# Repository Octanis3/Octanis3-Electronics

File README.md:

# Octanis3-Electronics

Contains PCB files of the Owl Monitoring Device. More information on http://nestbox.octanis.org/

## Folders
* *_admin*: General administrative documents (e.g. Sponsoring documents, Project proposals etc.)
* *Nestbox_v1*: First PCB version with Lighbarrier, 13MHz RFID, (untested) LORA module
* *Nextbox_v2*: Second PCB version using 125-134 kHz RFID

## Dependencies
* Created with KiCAD 4.0.4 stable
* BOM created with bom2groupedCsv.xsl plugin by Wolf Walter.
* Schematic parts managed with https://github.com/BPJWES/KiCAD_Partslist_editor

2017

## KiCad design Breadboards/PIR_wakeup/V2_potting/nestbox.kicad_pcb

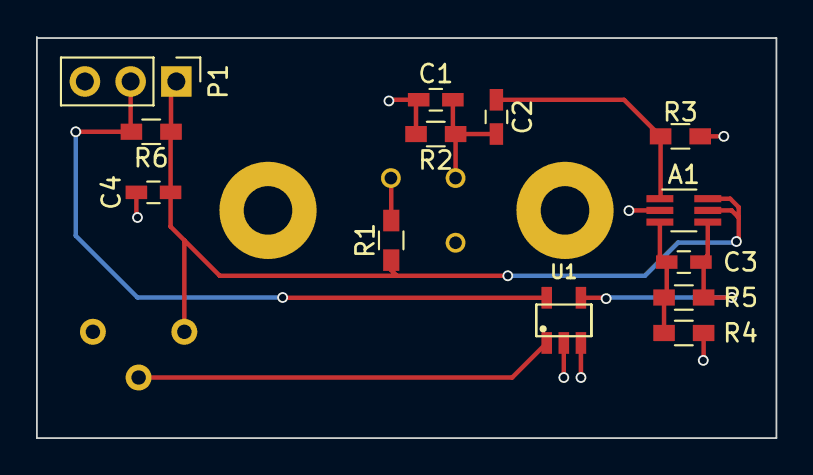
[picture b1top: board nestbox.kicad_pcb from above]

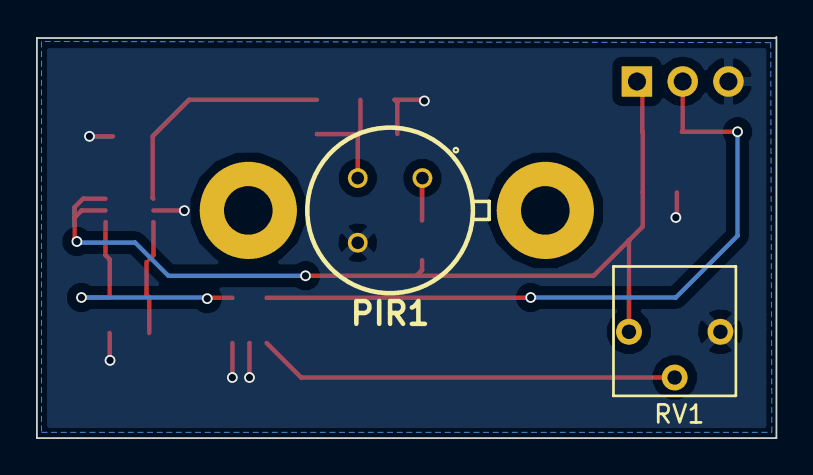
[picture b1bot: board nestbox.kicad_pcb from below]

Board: 2 copper layers, 41.1 x 22.3 mm, 15 parts (2 on the bottom side), 9 nets.

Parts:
A1: SOT-363_SC-70-6_Handsoldering
C1, C2, C3, C4: C_0603_HandSoldering
P1: Pin_Header_Straight_1x03_Pitch2.54mm
PIR1: IRA-S210ST01
R1, R2, R3, R4, R5, R6: R_0603_HandSoldering
RV1: Pot
U1: MAX9061

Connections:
GND: A1.2, C1.2, C4.2, P1.3, PIR1.3, R2.2, R3.2, R4.2, RV1.3, U1.2, U1.3
unnamed: A1.1, C2.1, R3.1
unnamed: A1.3, C3.2, R4.1, R5.2
unnamed: A1.4, C3.1, R5.1, U1.4
unnamed: A1.5, A1.6, C4.1, P1.1, R1.1, R6.1, RV1.1
unnamed: C1.1, C2.2, PIR1.2, R2.1
unnamed: P1.2, R6.2, U1.5
unnamed: PIR1.1, R1.2
unnamed: RV1.2, U1.1

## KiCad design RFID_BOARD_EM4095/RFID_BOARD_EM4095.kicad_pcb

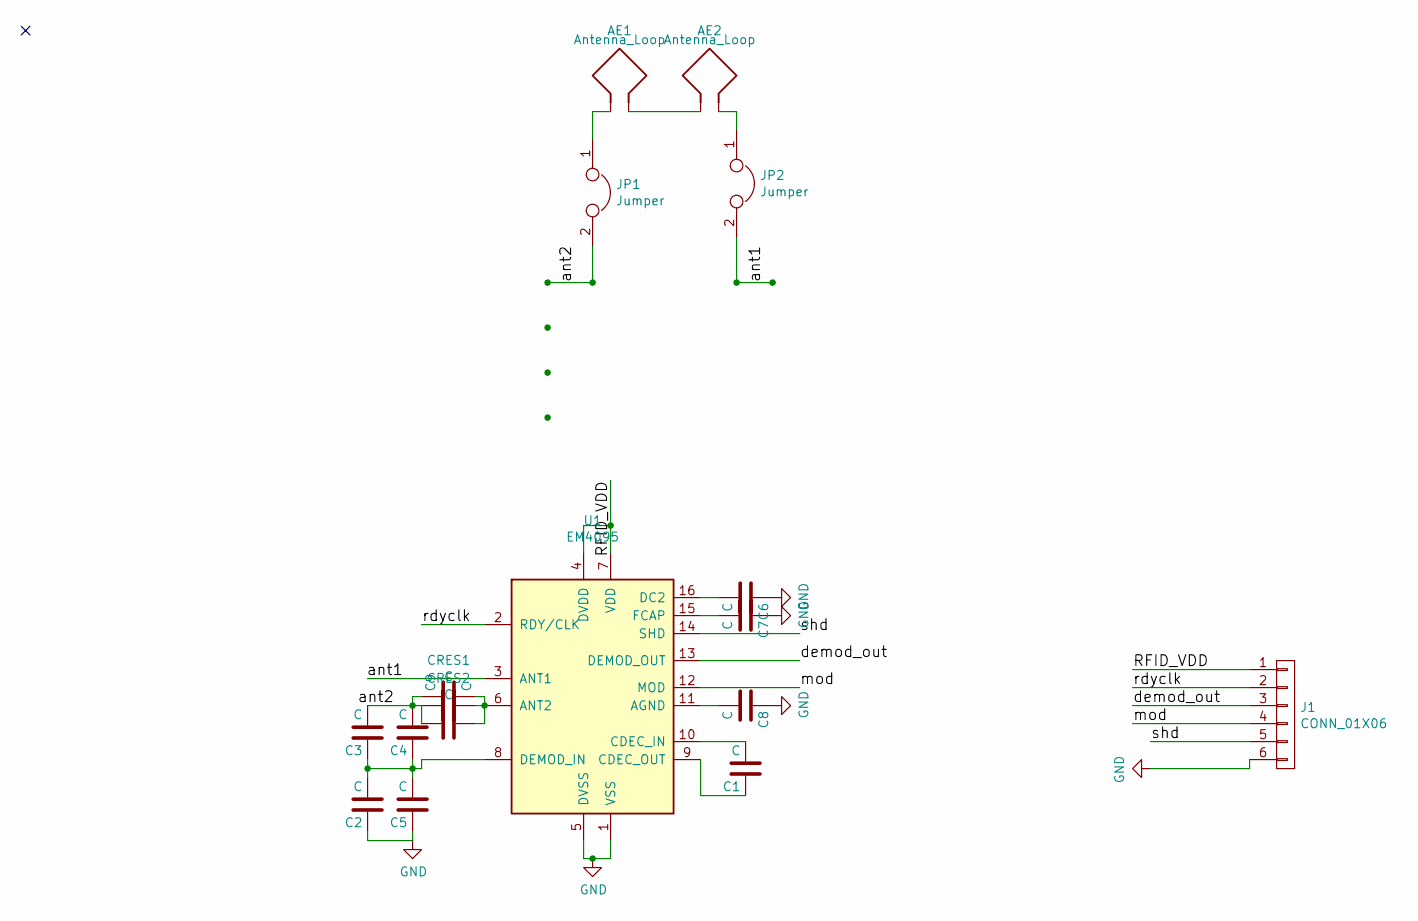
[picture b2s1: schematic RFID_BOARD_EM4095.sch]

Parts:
AE1, AE2: Antenna_Loop; 125kHz_PCB_Antenna
C1, C2, C3, C4, C5, C6, C7, C8, C9: C; C_0603
CRES1, CRES2: C; C_Rect_L7_W2_P5
J1: CONN_01X06; PINHEAD1-6
JP1, JP2: Jumper; Pin_Header_Straight_1x02_Pitch2.00mm
U1: EM4095; SOIC-16_3.9x9.9mm_Pitch1.27mm

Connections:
/RFID_VDD: J1.1, U1.4 (DVDD), U1.7 (VDD)
/ant1: JP2.2, U1.3 (ANT1)
/ant2: C3.2, C4.2, C9.1, CRES1.2, CRES2.2, JP1.2; also elsewhere on the board
/demod_out: J1.3, U1.13 (DEMOD_OUT)
/mod: J1.4, U1.12 (MOD)
/rdyclk: J1.2, U1.2 (RDY/CLK)
/shd: J1.5, U1.14 (SHD)
GND: C2.1, C5.1, C6.1, C7.1, C8.1, J1.6, U1.1 (VSS), U1.5 (DVSS)
unnamed: AE1.1, JP1.1
unnamed: AE1.2, AE2.2
unnamed: AE2.1, JP2.1
unnamed: C1.1, U1.9 (CDEC_OUT)
unnamed: C1.2, U1.10 (CDEC_IN)
unnamed: C2.2, C3.1, C4.1, C5.2, U1.8 (DEMOD_IN)
unnamed: C6.2, U1.16 (DC2)
unnamed: C7.2, U1.15 (FCAP)
unnamed: C8.2, U1.11 (AGND)
unnamed 17: C9.2, CRES1.1, CRES2.1, U1.6 (ANT2); also elsewhere on the board

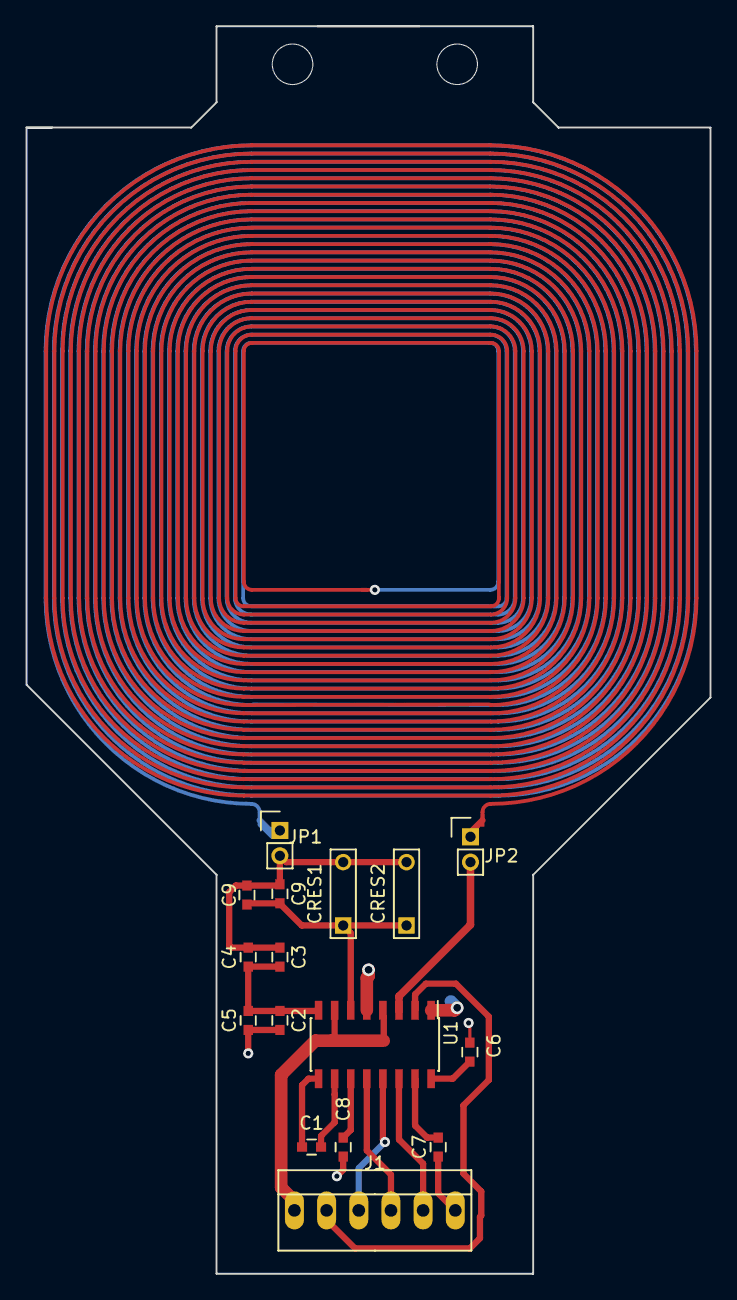
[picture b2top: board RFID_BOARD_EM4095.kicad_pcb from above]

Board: 2 copper layers, 54.0 x 98.5 mm, 18 parts (1 on the bottom side), 18 nets.

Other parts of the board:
C9#2: C; C_0603

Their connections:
/ant2: C9#2.1; also elsewhere on the board
unnamed 17: C9#2.2; also elsewhere on the board

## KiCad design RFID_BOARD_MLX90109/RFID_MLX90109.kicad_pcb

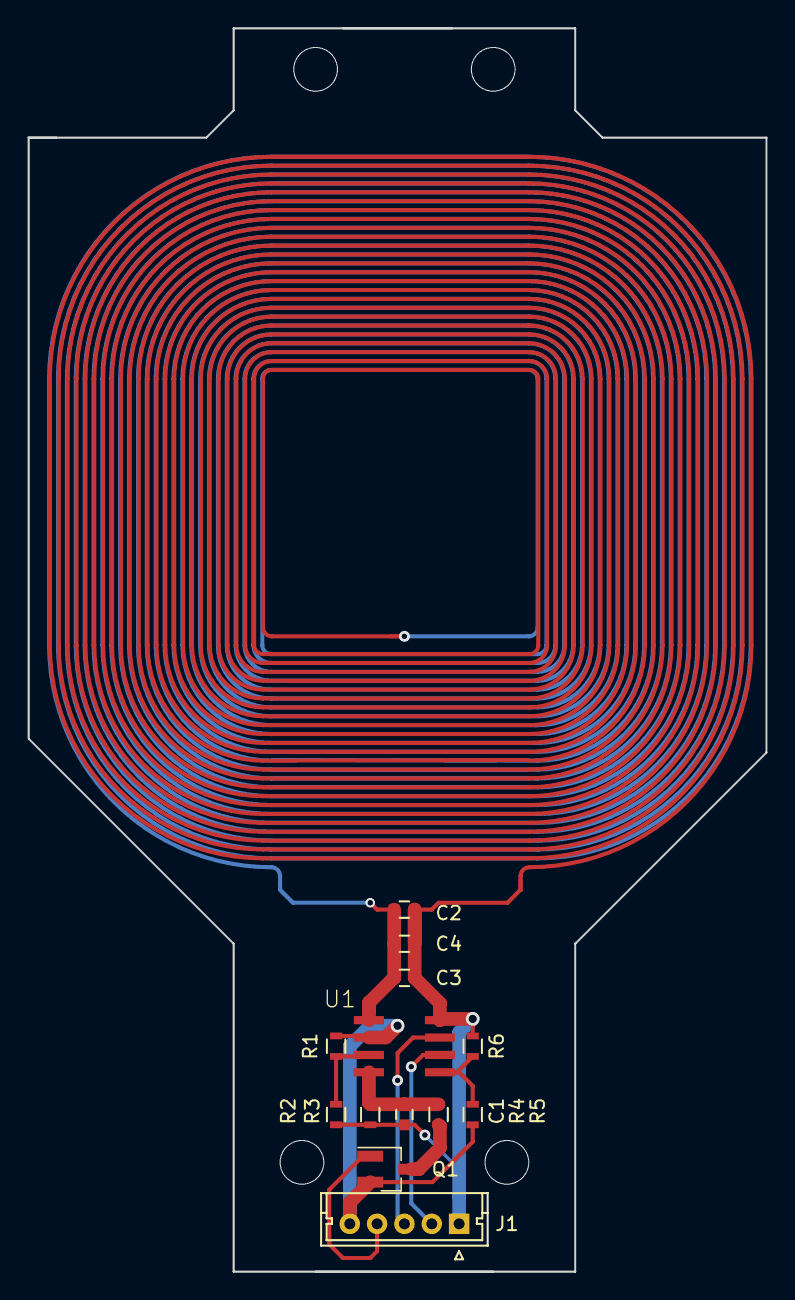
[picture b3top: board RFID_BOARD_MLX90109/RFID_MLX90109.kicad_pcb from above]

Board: 2 copper layers, 54.0 x 91.0 mm, 15 parts (1 on the bottom side), 11 nets.

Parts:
AE1, AE2: Antenna_Loop; 125kHz_PCB_Antenna
C1, C2, C3, C4: C; C_0603
J1: CONN_01X05; Molex_MicroLatch-53253-0570_05x2.00mm_Straight
Q1: Q_NMOS_GSD; SOT-23_Handsoldering
R1, R2, R5, R6: R; R_0603
R3: 100k; R_0603
R4: 36k; R_0603
U1: MLX90109; SO8

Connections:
/RFID_ANT: AE1.1, C2.2, C3.2, C4.2, U1.1
/RFID_CLOCK: J1.2, U1.6
/RFID_DATA: J1.3, U1.7
/RFID_MODE: R5.2, R6.1, U1.5
/RFID_SPEED: R1.1, R2.1, U1.3
/RFID_VDD: AE2.1, C1.2, C2.1, C3.1, C4.1, J1.1, R2.2, R3.2, R6.2, U1.8
GND: J1.5, Q1.2, R1.2, R5.1, U1.2
unnamed: AE1.2, AE2.2
unnamed: C1.1, R3.1, R4.2, U1.4
unnamed: Q1.3, R4.1
RFID_MODU_N: J1.4, Q1.1

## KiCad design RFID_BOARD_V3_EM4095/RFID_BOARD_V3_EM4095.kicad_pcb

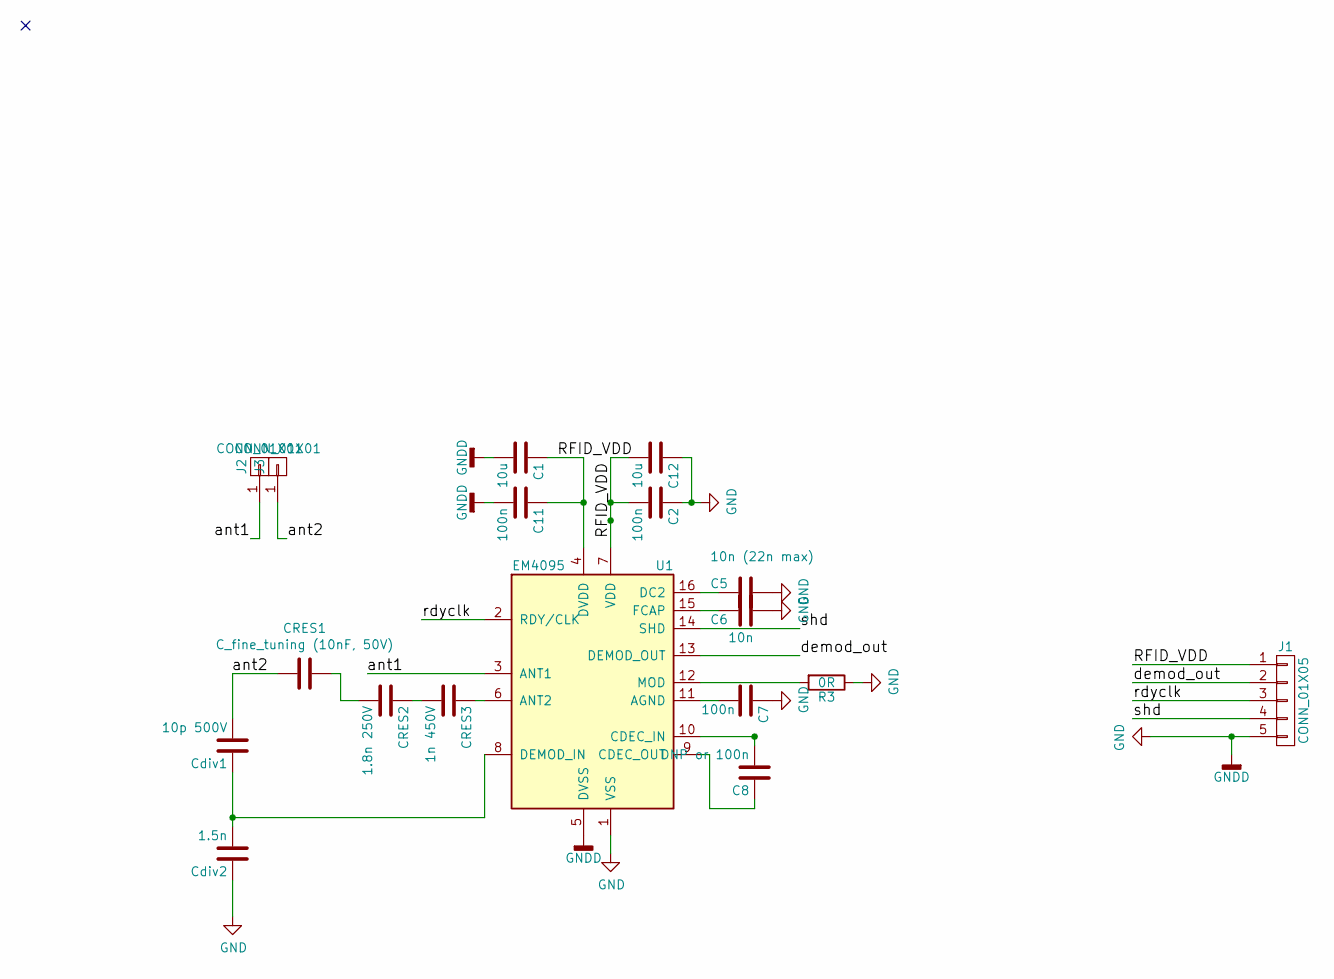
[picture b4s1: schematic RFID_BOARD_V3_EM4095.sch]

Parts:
C1, C12: 10u; C_0805
C2, C7, C11: 100n; C_0603
C5: 10n (22n max); C_0603
C6: 10n; C_0603
C8: DNP or 100n; C_0603
CRES1: C_fine_tuning (10nF, 50V); C_0603
CRES2: 1.8n 250V; C_0805; MPN C0805C182JAGAC
CRES3: 1n 450V; C_0805; MPN C0805C102JAGACTU or CC0805JKNPOBBN102
Cdiv1: 10p 500V; C_0805; MPN C0805C100KBRACTU
Cdiv2: 1.5n; C_0603
J1: CONN_01X05; Pin_Header_Straight_1x05_Pitch2.54mm
J2, J3: CONN_01X01; Measurement_Point_Square-SMD-Pad_Small
R3: 0R; R_0603
U1: EM4095; SOIC-16_3.9x9.9mm_Pitch1.27mm

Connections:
/RFID_VDD: C1.1, C2.2, C11.1, C12.2, J1.1, U1.4 (DVDD), U1.7 (VDD)
/ant1: J2.1, U1.3 (ANT1)
/ant2: CRES1.2, Cdiv1.2, J3.1
/demod_out: J1.2, U1.13 (DEMOD_OUT)
/rdyclk: J1.3, U1.2 (RDY/CLK)
/shd: J1.4, U1.14 (SHD)
GND: C1.2, C2.1, C5.1, C6.1, C7.1, C11.2, C12.1, Cdiv2.1, J1.5, R3.1, U1.1 (VSS), U1.5 (DVSS)
unnamed: C5.2, U1.16 (DC2)
unnamed: C6.2, U1.15 (FCAP)
unnamed: C7.2, U1.11 (AGND)
unnamed: C8.1, U1.9 (CDEC_OUT)
unnamed: C8.2, U1.10 (CDEC_IN)
unnamed: CRES1.1, CRES2.2
unnamed: CRES2.1, CRES3.2
unnamed: CRES3.1, U1.6 (ANT2)
unnamed: Cdiv1.1, Cdiv2.2, U1.8 (DEMOD_IN)
unnamed: R3.2, U1.12 (MOD)

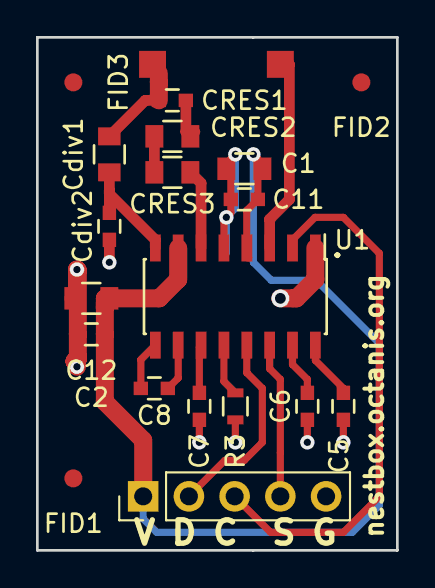
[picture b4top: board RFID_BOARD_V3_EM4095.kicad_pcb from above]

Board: 2 copper layers, 20.0 x 28.5 mm, 21 parts (0 on the bottom side), 17 nets.

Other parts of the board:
FID1, FID2, FID3: Fiducial_1mm_Dia_2.54mm_Outer_CopperTop

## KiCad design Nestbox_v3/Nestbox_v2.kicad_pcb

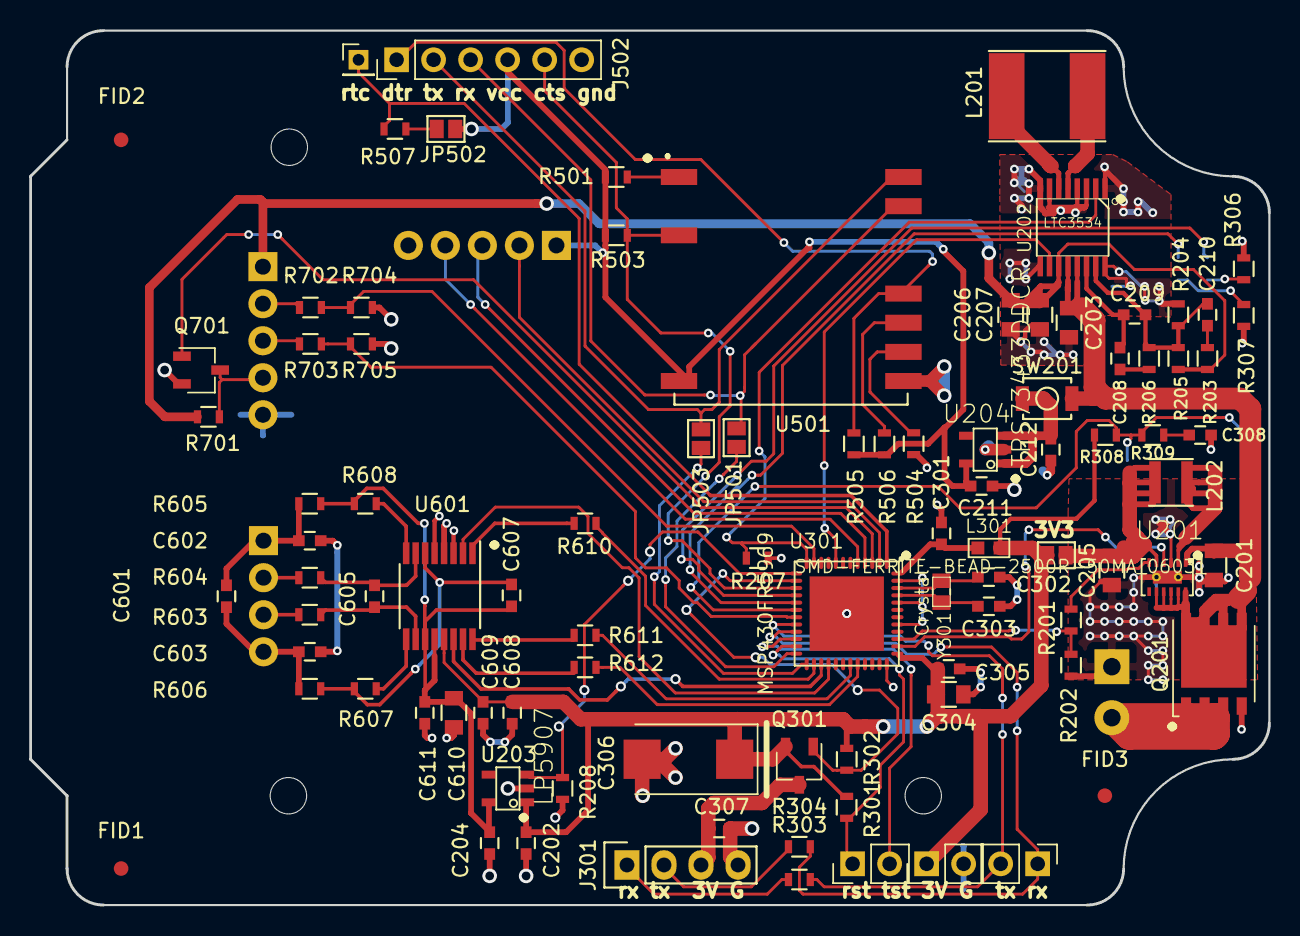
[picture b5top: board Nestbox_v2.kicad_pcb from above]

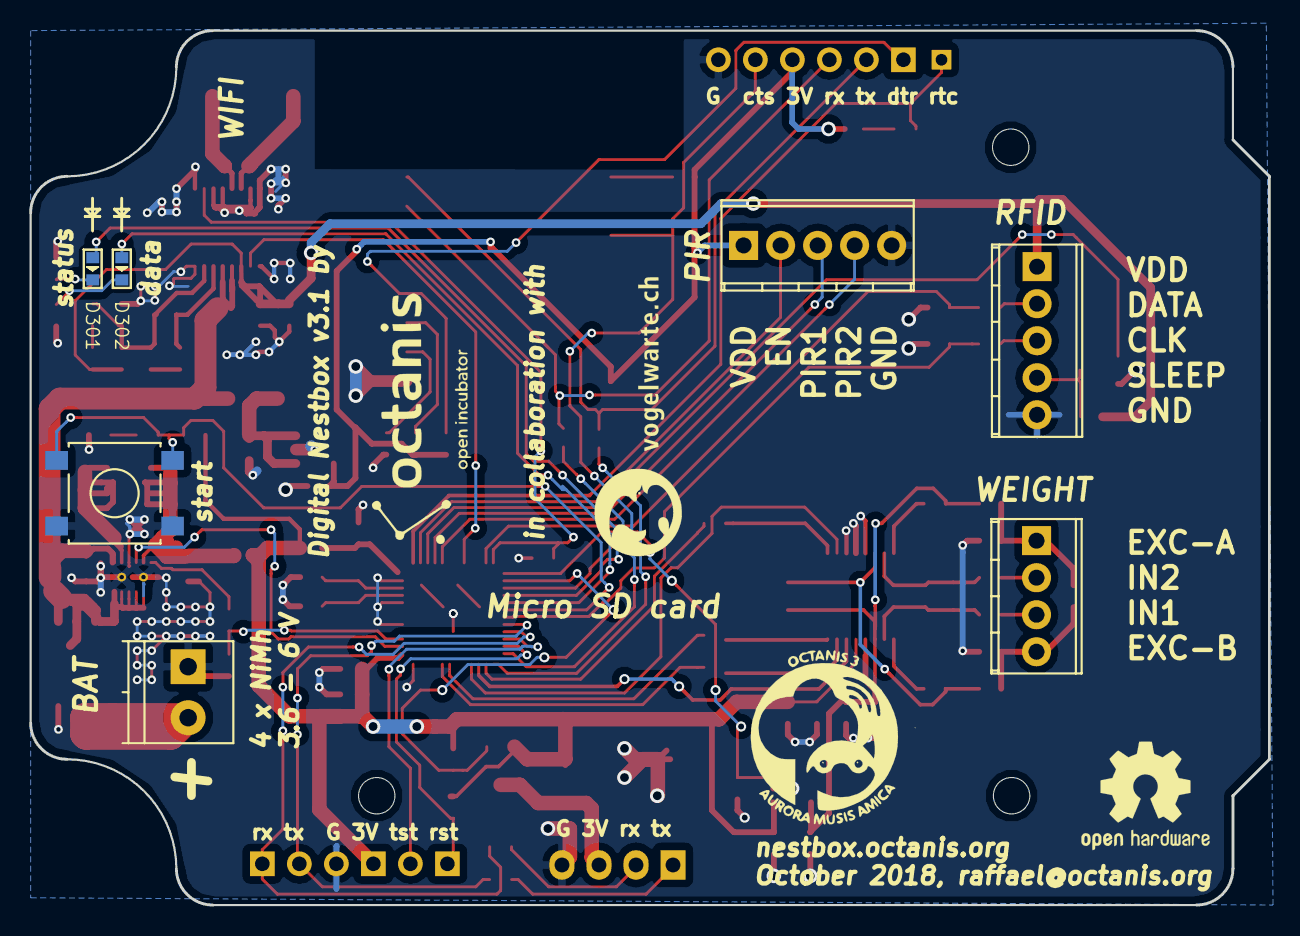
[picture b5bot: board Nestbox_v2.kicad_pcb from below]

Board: 2 copper layers, 85.0 x 60.0 mm, 100 parts (7 on the bottom side), 76 nets.

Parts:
C201, C203, C205, C206, C207, C304, C610: 10u; C_0805
C202, C204, C212, C601, C607, C608: 1u; C_0603
C208: 330p; C_0603
C209: 10p; C_0603
C210: 33p; C_0603
C211: 2.2u; C_0603
C301, C305, C307, C308, C609: 100n; C_0603
C302, C303: 25p; C_0603
C306: 100u; CP_Tantalum_Case-D_EIA-7343-31_Reflow
C602, C603: 100n 1%; C_0603
C605: 100n 1% DNP; C_0603
C611: 10n; C_0603
D301: SMD-LED-CLEAR-GREEN_0603_; LED-0603
D302: SMD-LED-CLEAR-BLUE_0603_; LED-0603
FID1, FID2, FID3: Fiducial_1mm_Dia_2.54mm_Outer_CopperTop
J201: BATT_CONN_01X02; TerminalBlock_Pheonix_PT-3.5mm_2pol
J301: CONN_01X04; Pin_Header_Straight_1x04
J402: CONN_01X05; TerminalBlock_Pheonix_MPT-2.54mm_5pol
J502: CONN_01X06; Pin_Header_Straight_1x06_Pitch2.54mm
J601: LOAD_CELL_CONN_01X04; TerminalBlock_Pheonix_MPT-2.54mm_4pol
J701: RFID_CONN_01X05; TerminalBlock_Pheonix_MPT-2.54mm_5pol
JP203: Jumper_3V3; GS2
JP501, JP502, JP503: Jumper; GS2
L201: 5uH; Inductor_Taiyo-Yuden_NR-60xx_HandSoldering
L202: 4.7uH; Inductor_Taiyo-Yuden_NR-30xx
L301: SMD-FERRITE-BEAD-2500R-50MA_0603_; L0603
P301: RX/TX; Socket_Strip_Straight_1x02_Pitch2.54mm
P302: TST/RST; Socket_Strip_Straight_1x02_Pitch2.54mm
P303: DEBUG_3V3; Socket_Strip_Straight_1x02_Pitch2.54mm
Q201: TPH1R712MDL1Q; TDSON-8-1_HandSoldering
Q301: NTR3A052PZT1G; TSOT-23
Q701: DMG3402L; TSOT-23
R201, R207, R208, R302, R507, R701, R704, R705: 82k; R_0603
R202, R301, R702, R703: 47k; R_0603
R203, R308, R309, R501, R503, R504, R505, R506: 10k; R_0603
R204: 162k 1%; R_0603
R205: 649k 1%; R_0603
R206: 15k; R_0603
R303, R304: 0R; R_0603
R306, R307: 1k; R_0603
R603, R604: 1k 1% --> short to 0R; R_0603
R605, R606: 100R 1%; R_0603
R607, R608: DNP; R_0603
R610, R611, R612: 47R; R_0603
SW201: external_button; SW_SPST_B3U-1000P
SW301: SMD-BUTTON_2P-3.0X2.5X1.2+0.4MM_; SW_SPST_B3S-1000
TP_RTC301: CONN_01X01; Socket_Strip_Straight_1x01_Pitch2.00mm
U201: TPS62745; WSON_3x2mm_12pin
U202: LTC3534; SSOP16-0.635-5X4MM
U203: LP5907; SOT23-5
U204: TPS73433DDCR; SOT23-5
U301: MSP430FR5969; S-PVQFN-N48
U501: ESP-12S; ESP-12E_SMD_UART_ONLY
U601: ADS1220; TSSOP-16_4.4x5mm_Pitch0.65mm
Y301: Crystal; X2-SMD-L2.0X1.2X0.55MM

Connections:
+3V3: C202.1, C304.2, C305.2, C306.1, C608.1, C609.2, JP203.2, L301.2, P303.1, Q301.2, R301.2, R302.1, R308.1, U203.1, U301.37, U601.13
+5V: C206.1, C207.1, J701.1, R203.2, R205.1, R701.2, U202.11
+BATT: C201.1, C203.1, Q201.3, SW201.1, U201.1, U201.8, U201.9, U201.10, U201.11, U201.12, U202.12, U202.13
/Communication/DTR: J502.1, R505.2, U501.12
/Communication/ESP12_ENABLE: J502.5, R503.1, U301.15, U501.3
/Communication/ESP12_RX: JP501.1, U301.24
/Communication/ESP12_TX: JP503.1, U301.25
/Communication/ESP12_VCC_sense: R507.2, TP_RTC301.1, U301.1
/Communication/RX: J502.3, JP501.2, U501.15
/Communication/TX: J502.2, JP503.2, U501.16
/Control/5V_ENABLE: R207.2, U202.2, U301.12
/Control/AVCC: C301.1, L301.1, U301.48
/Control/BAT_TEST_ENABLE: U201.4, U301.38
/Control/DBG_LED1: D301.+, U301.16
/Control/DBG_LED2: D302.+, U301.17
/Control/DBG_Switch: R308.2, R309.1, SW301.2, U301.18
/Control/HK_BAT_V: R201.1, R202.2, U301.39
/Control/LOADCELL_SPI_CS: U301.28, U601.2
/Control/RFID_CLK: R702.1, R704.2, U301.11
/Control/RFID_DATA: R703.2, R705.1, U301.19
/Control/RFID_SLEEP_N: Q701.1, U301.3
/Control/RX: P301.1, R304.1, U301.21
/Control/SD_CARD_ENABLE: Q301.1, R302.2, U301.14
/Control/SPI_CLK: R610.1, U301.26
/Control/SPI_MISO: R612.1, U301.32
/Control/SPI_MOSI: R611.1, U301.31
/Control/TX: P301.2, R303.1, U301.20
/Load_Cell/AIN1: C605.1, R603.1, U601.10
/Load_Cell/AIN2: C605.2, R604.1, U601.7
/Load_Cell/DRDY_N: U301.27, U601.14
/Load_Cell/EXC_A: C601.1, C602.1, J601.1, R605.2
/Load_Cell/EXC_B: C601.2, C603.1, J601.4, R606.2
/Load_Cell/conn2: J601.2, R604.2
/Load_Cell/conn3: J601.3, R603.2
/PIR_EN: J402.2, U301.2
/PIR_OUT1: J402.3, U301.4
/PIR_OUT2: J402.4, U301.5
/Power/5V_PWM: U202.10, U301.8
/Power/LDO_EN: R208.2, U203.3, U301.13
/Power/batt_in: J201.2, Q201.1
GND: C201.2, C202.2, C203.2, C204.2, C205.2, C206.2, C207.2, C211.2, C212.2, C301.2, C302.2, C303.2, C304.1, C305.1, C306.2, C307.2, C308.2, C602.2, C603.2, C608.2, C609.1, C610.1, C611.1, J201.1, J301.4, J402.5, J502.6, J701.5, P303.2, Q201.2, Q701.2, R202.1, R204.1, R207.1, R208.1, R306.2, R307.2, R504.1, R704.1, R705.2, SW301.1, U201.3, U201.GND1, U201.GND2, U202.1, U202.3, U202.4, U202.7, U202.8, U202.9, U202.16, U203.2, U204.2, U301.36, U301.41, U301.44, U301.47, U301.VSS_, U501.9, U601.3, U601.4, U601.5
unnamed: C205.1, JP203.1, L202.2, U201.5
unnamed: C208.1, R206.1
unnamed: C208.2, C209.2, U202.14
unnamed: C209.1, C210.2, R204.2, R205.2, R206.2, U202.15
unnamed: C210.1, R203.1
unnamed: C212.1, SW201.2, U204.1, U204.3
unnamed: C302.1, U301.46, Y301.1
unnamed: C303.1, U301.45, Y301.2
unnamed: C307.1, J301.3, Q301.3
unnamed: C308.1, R309.2
unnamed: C607.2, R606.1, R607.2, U601.6
unnamed: D301.-, R306.1
unnamed: D302.-, R307.1
unnamed: J301.1, R303.2
unnamed: J301.2, R304.2
unnamed: J701.2, R702.2
unnamed: J701.3, R703.1
unnamed: J701.4, Q701.3, R701.1
unnamed: JP502.2, R507.1
unnamed: L201.1, U202.5
unnamed: L201.2, U202.6
unnamed: L202.1, U201.2
unnamed: P302.1, R301.1, U301.23
unnamed: P302.2, U301.22
unnamed: R201.2, U201.6
unnamed: R501.2, U501.1
unnamed: R504.2, U501.10
unnamed: R506.2, U501.11
unnamed: R607.1, U601.9
unnamed: R608.1, U601.8
unnamed: R610.2, U601.1
unnamed: R611.2, U601.16
unnamed: R612.2, U601.15
VAA: C204.1, C607.1, C610.2, C611.2, R605.1, R608.2, U203.5, U601.11, U601.12
VDDA: C211.1, J402.1, J502.4, JP502.1, R501.1, R503.2, R505.1, R506.1, U204.5, U501.8

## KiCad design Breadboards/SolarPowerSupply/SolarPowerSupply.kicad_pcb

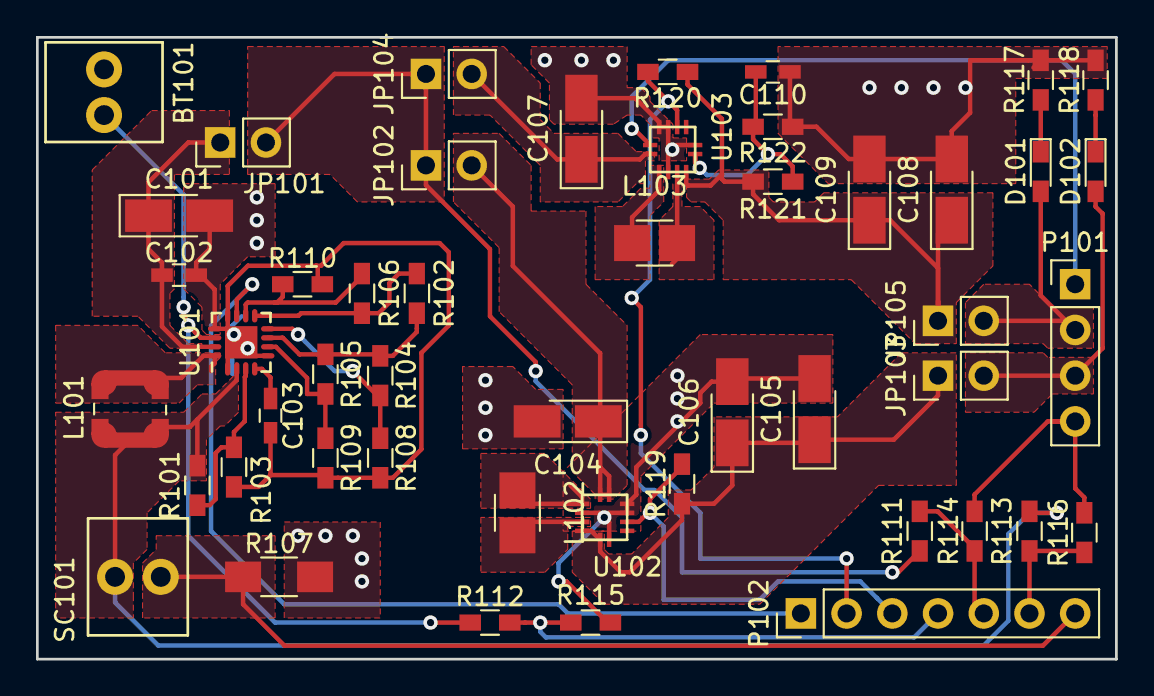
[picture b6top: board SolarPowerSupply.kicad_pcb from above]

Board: 2 copper layers, 59.9 x 34.5 mm, 49 parts (0 on the bottom side), 34 nets.

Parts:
BT101: Battery; TE_282834-2
C101: 4.7u; C_SMD_2012_Hand
C102: 100n; C_0603_HandSoldering
C103: 10n; C_0603_HandSoldering
C104, C105, C106, C107, C108, C109: 10u; C_SMD_2012_Hand
C110: 10p; C_0603_HandSoldering
D101, D102: LED; LED_0603_HandSoldering
JP101, JP102, JP103, JP104, JP105: Jumper; Pin_Header_Straight_1x02_Pitch2.54mm
L101: 22u; L_Wuerth_WE-TPC-3816
L102, L103: 1.5u; L_2520_HandSoldering
P101: CONN_01X04; Pin_Header_Straight_1x04_Pitch2.54mm
P102: CONN_01X07; Pin_Header_Straight_1x07_Pitch2.54mm
R101, R102, R103, R104, R105, R106, R108, R109, R110, R111, R112, R113, R114, R115, R116, R117, R118, R121, R122: R; R_0603_HandSoldering
R107: 1E; R_1206_HandSoldering
R119, R120: 1M; R_0603_HandSoldering
SC101: Solar_Cells; TE_282834-2
U101: bq25504; QFN-16-1EP_3x3mm_Pitch0.5mm
U102: TPS63051; VQFN_12_2.5x2.5mm
U103: TPS63050; VQFN_12_2.5x2.5mm

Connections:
5V_Enable: P101.1, U103.11
+3V3: D102.2, JP103.2, P101.3
+5V: D101.2, JP105.2, P101.2
/VBat: BT101.1, R112.1, U101.14
/VBus: JP101.2, JP102.1, JP104.1, R111.1
/VSolar: L101.1, R101.1, R113.1, SC101.1, U101.2
BAT_OK: P102.1, U101.11
GND: BT101.2, C101.2, C102.2, C103.2, C104.2, C105.2, C106.2, C107.2, C108.2, C109.2, C110.2, P101.4, R103.2, R107.2, R108.2, R109.2, R110.2, R114.2, R115.2, R116.2, R117.2, R118.2, R122.1, U101.1, U101.5, U101.12, U101.13, U101.17, U102.2, U102.6, U102.9, U102.10, U103.2, U103.6, U103.9, U103.10
HK_BAT_V: P102.4, R112.2, R115.1
HK_BUS_V: P102.5, R111.2, R114.1
HK_SOLAR_I: P102.7, R107.1, SC101.2
HK_SOLAR_V: P102.6, R113.2, R116.1
unnamed: C101.1, C102.1, JP101.1, U101.15
unnamed: C103.1, U101.4
unnamed: C104.1, JP102.2, U102.11, U102.12
unnamed: C105.1, C106.1, JP103.1, R119.1, U102.4, U102.5
unnamed: C107.1, JP104.2, U103.12
unnamed: C108.1, C109.1, JP105.1, R120.1, R121.1, U103.4
unnamed: C110.1, R121.2, R122.2, U103.5
unnamed: D101.1, R117.1
unnamed: D102.1, R118.1
unnamed: L101.2, U101.16
unnamed: L102.1, U102.1
unnamed: L102.2, U102.3
unnamed: L103.1, U103.1
unnamed: L103.2, U103.3
unnamed: R101.2, R103.1, U101.3
unnamed: R102.1, R104.1, R105.1, U101.7
unnamed: R102.2, R106.1, U101.9
unnamed: R104.2, R108.1, U101.8
unnamed: R105.2, R109.1, U101.6
unnamed: R106.2, R110.1, U101.10
PGOOD_3.3: P102.3, R119.2, U102.8
PGOOD_5: P102.2, R120.2, U103.8

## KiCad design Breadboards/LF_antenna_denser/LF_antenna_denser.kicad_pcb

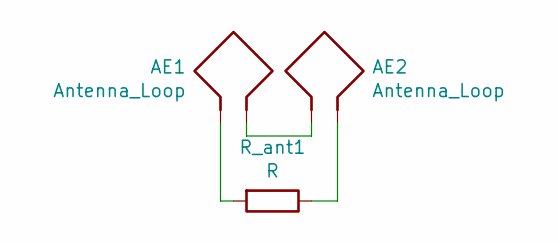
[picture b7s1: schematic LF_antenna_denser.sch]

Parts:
AE1, AE2: Antenna_Loop; 125kHz_PCB_Antenna_wide
R_ant1: R; Resistor_Horizontal_RM25mm

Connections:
unnamed: AE1.1, AE2.1
unnamed: AE1.2, R_ant1.2
unnamed: AE2.2, R_ant1.1

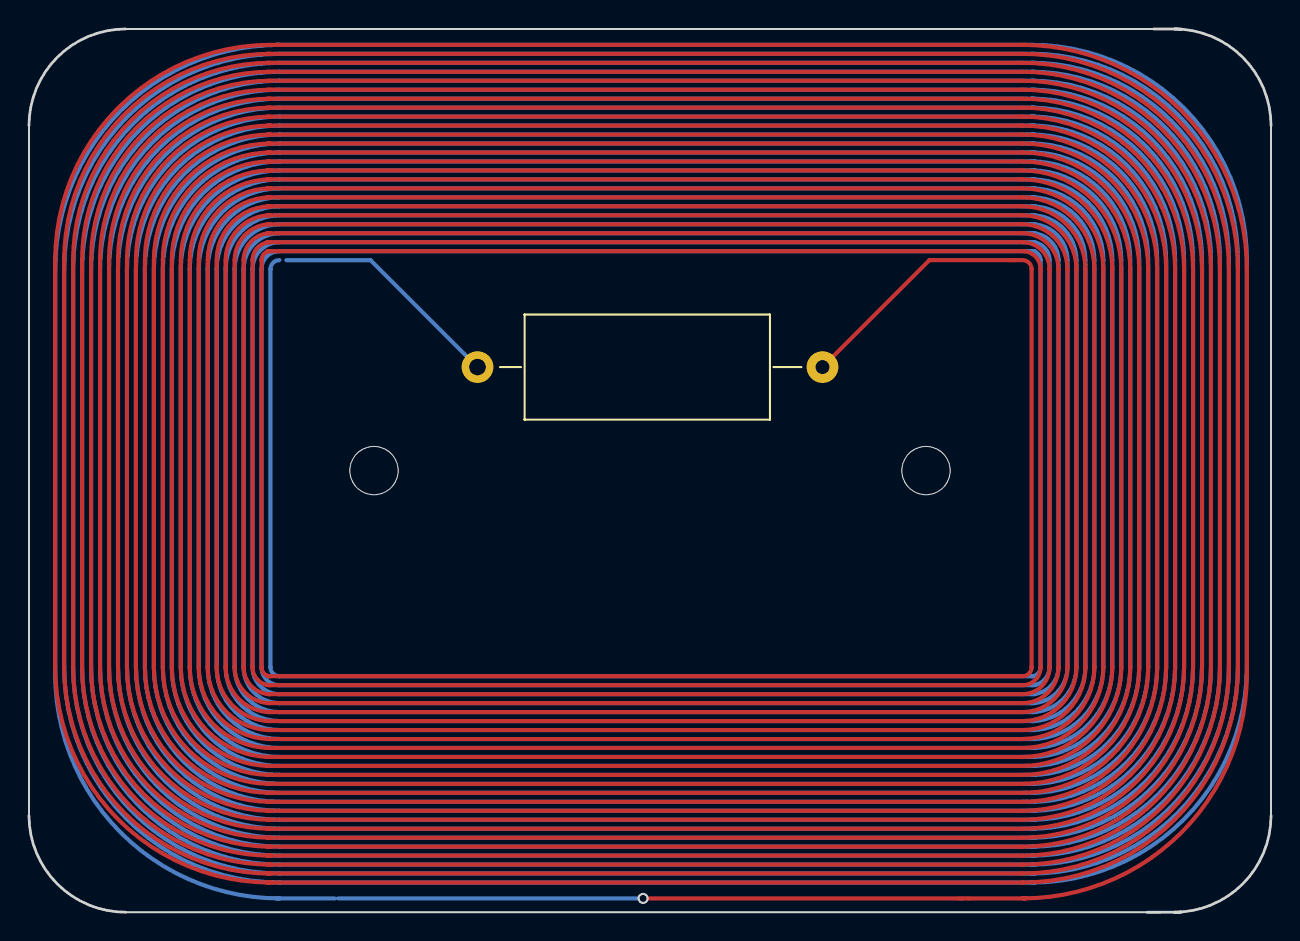
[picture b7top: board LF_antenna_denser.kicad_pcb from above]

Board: 2 copper layers, 90.0 x 64.0 mm, 3 parts (1 on the bottom side), 3 nets.

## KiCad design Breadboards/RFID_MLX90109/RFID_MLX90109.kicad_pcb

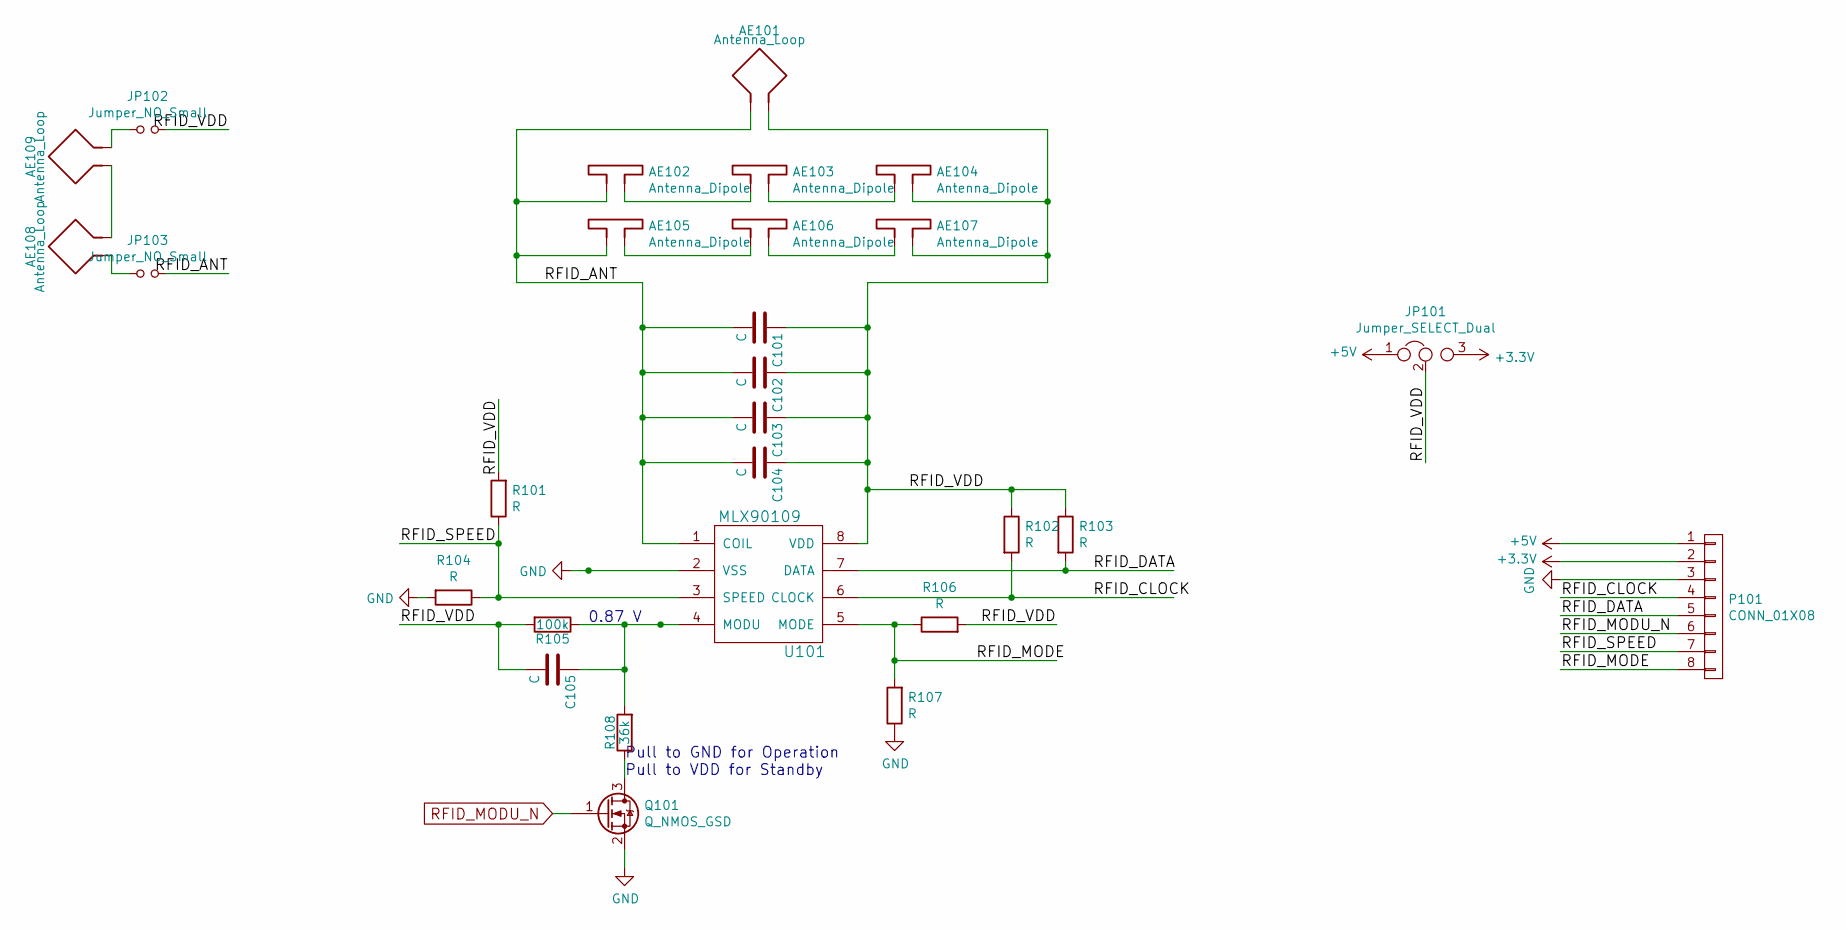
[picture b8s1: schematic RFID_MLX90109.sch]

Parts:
AE101: Antenna_Loop; R_Axial_DIN0411_L9.9mm_D3.6mm_P25.40mm_Horizontal
AE102, AE103, AE104, AE105, AE106, AE107: Antenna_Dipole; TDK_B82450A
AE108, AE109: Antenna_Loop; 125kHz_PCB_Antenna
C101, C102: C; C_Rect_L7.0mm_W3.5mm_P5.00mm
C103, C104, C105: C; C_0805_HandSoldering
JP101: Jumper_SELECT_Dual; Pin_Header_Straight_1x03_Pitch2.54mm
JP102, JP103: Jumper_NO_Small; Pin_Header_Straight_1x02_Pitch2.54mm
P101: CONN_01X08; Pin_Header_Straight_1x08_Pitch2.54mm
Q101: Q_NMOS_GSD; SOT-23_Handsoldering; Mouser-Part 726-BSS127H6327
R101, R102, R103, R104, R106, R107: R; R_0603_HandSoldering
R105: 100k; R_0603_HandSoldering
R108: 36k; R_0603_HandSoldering
U101: MLX90109; SOIC-8_3.9x4.9mm_Pitch1.27mm

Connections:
+3V3: JP101.3, P101.2
+5V: JP101.1, P101.1
/RFID_ANT: AE101.1, AE102.1, AE105.1, C101.2, C102.2, C103.2, C104.2, JP103.2, U101.1 (COIL)
/RFID_CLOCK: P101.4, R102.2, U101.6 (CLOCK)
/RFID_DATA: P101.5, R103.2, U101.7 (DATA)
/RFID_MODE: P101.8, R106.1, R107.2, U101.5 (MODE)
/RFID_SPEED: P101.7, R101.1, R104.1, U101.3 (SPEED)
/RFID_VDD: AE101.2, AE104.2, AE107.2, C101.1, C102.1, C103.1, C104.1, C105.2, JP101.2, JP102.2, R101.2, R102.1, R103.1, R105.2, R106.2, U101.8 (VDD)
GND: P101.3, Q101.2 (S), R104.2, R107.1, U101.2 (VSS)
unnamed: AE102.2, AE103.1
unnamed: AE103.2, AE104.1
unnamed: AE105.2, AE106.1
unnamed: AE106.2, AE107.1
unnamed: AE108.1, JP103.1
unnamed: AE108.2, AE109.2
unnamed: AE109.1, JP102.1
unnamed: C105.1, R105.1, R108.2, U101.4 (MODU)
unnamed: Q101.3 (D), R108.1
RFID_MODU_N: P101.6, Q101.1 (G)

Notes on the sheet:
Pull to GND for Operation Pull to VDD for Standby
0.87 V

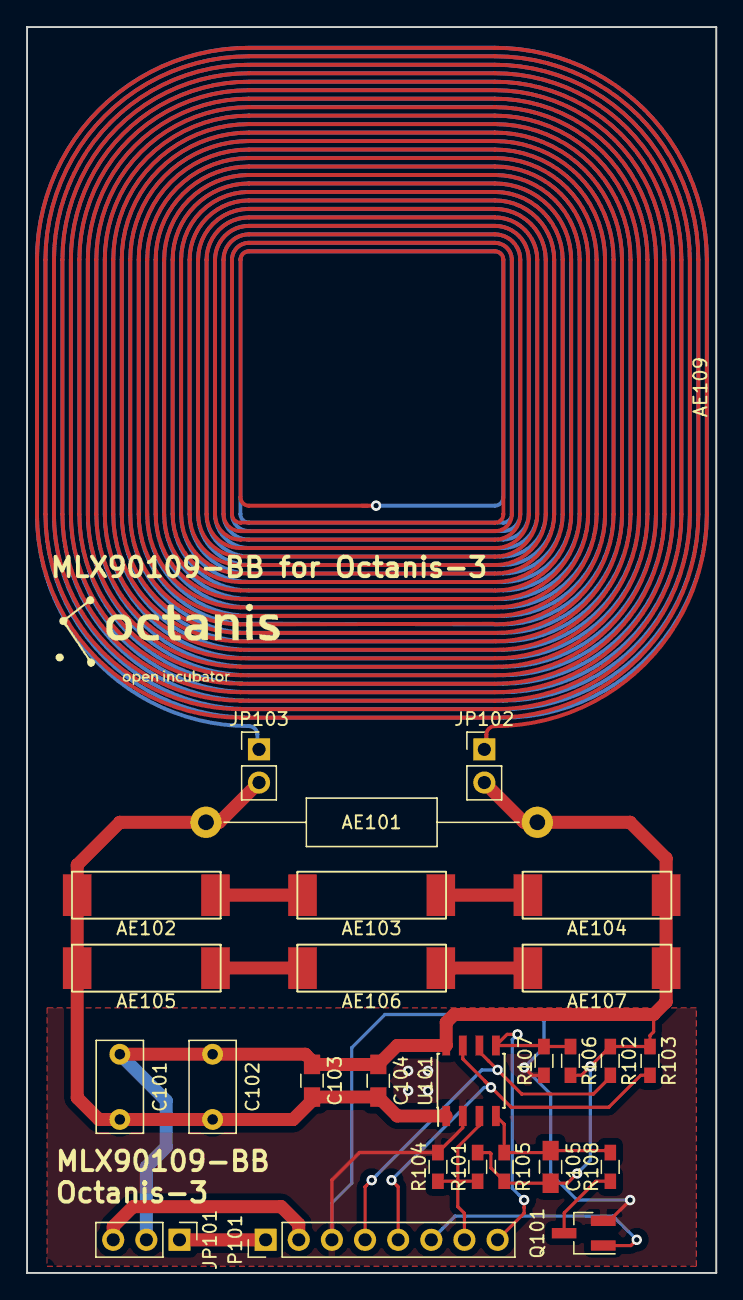
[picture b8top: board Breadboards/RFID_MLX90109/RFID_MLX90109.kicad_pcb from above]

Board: 2 copper layers, 52.8 x 95.5 mm, 28 parts (1 on the bottom side), 19 nets.
